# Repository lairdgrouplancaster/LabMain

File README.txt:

How to use this repository:
(Note: All commands are to be entered without quotation marks)

First off, you will need to install Git onto your local machine. Follow this link: "https://git-scm.com/" and download the appropriate version. If unsure whether git is installed on your local machine, open a command prompt and type: "git --version" and see whether it is installed. 

To start with, open up either the command prompt or GitBash and configure your Git username and email, which will be used to identify you as the author for each commit. This is done by entering the following: "git config --global user.name "YOUR_USERNAME"" and "git config --global user.email "YOUR_EMAIL@example.com""

Once this has been done, you can clone the repository to your local device by inputting the following command: "git clone https://github.com/lairdgrouplancaster/LabMain.git" which will then copy all of the files from the repository and place them in a folder of the same name. 

Once cloned, you can navigate to the directory in the command prompt, and then check to see your remote repositories by using: "git remote -v" This will usually show what remote repository it is (usually origin). If this isn't showing, you can manually add these repositories. 

AT THE START OF EACH SESSION: Ensure that you have an up-to-date copy of the repository by using: "git pull origin master"

To check the changes made in the local directory, you can use "git status" to check any modifications that you have made to the file itself, and use "git diff" to view the differences between the local changes to the repository versions that were previously cloned/pulled

You can add changes to the local version of the repository by using the following command: "git add FILE OR FOLDER" or "git add ." to ready either a file, folder or all files and folders for commiting. Then input: "git commit -m "COMMENT ON CHANGE AND INTENTION"" 

To push all of the local commits to the remote repository on GitHub, you can use the following command: "git push origin master", where you can replace origin for the name of a different remote repository and master for a different branch. 

All of this can also be done in the browser as well, and any additional pieces of information (Creating branches, forks etc.) can be found online, usually on the GitHub website itself.

Using a previous version of the repository:

After cloning the repository, look at the recent logs by using the command: "git log --oneline". Select the version of the roll back you want, and then make note of the first 5 characters of the unique number and use: "git checkout (5 characters)". Alternatively, you can use this function based on dates instead, for example if I wanted to revert back 10 days ago, I would input: "git checkout @{10.days.ago}"

Current Files: 

.gitignore: This file tells Git what files and folders to ignore when pulling or pushing updates. Currently only ignores the cache folder for Python.
LICENSE: This is where all licenses for software can be found, and can be added. Currently contains license for GNU
README: Current file, explains how to get started and what files are contained in this repository

Current Folders:

LiamColman: Liam's work uploaded onto Github for storage

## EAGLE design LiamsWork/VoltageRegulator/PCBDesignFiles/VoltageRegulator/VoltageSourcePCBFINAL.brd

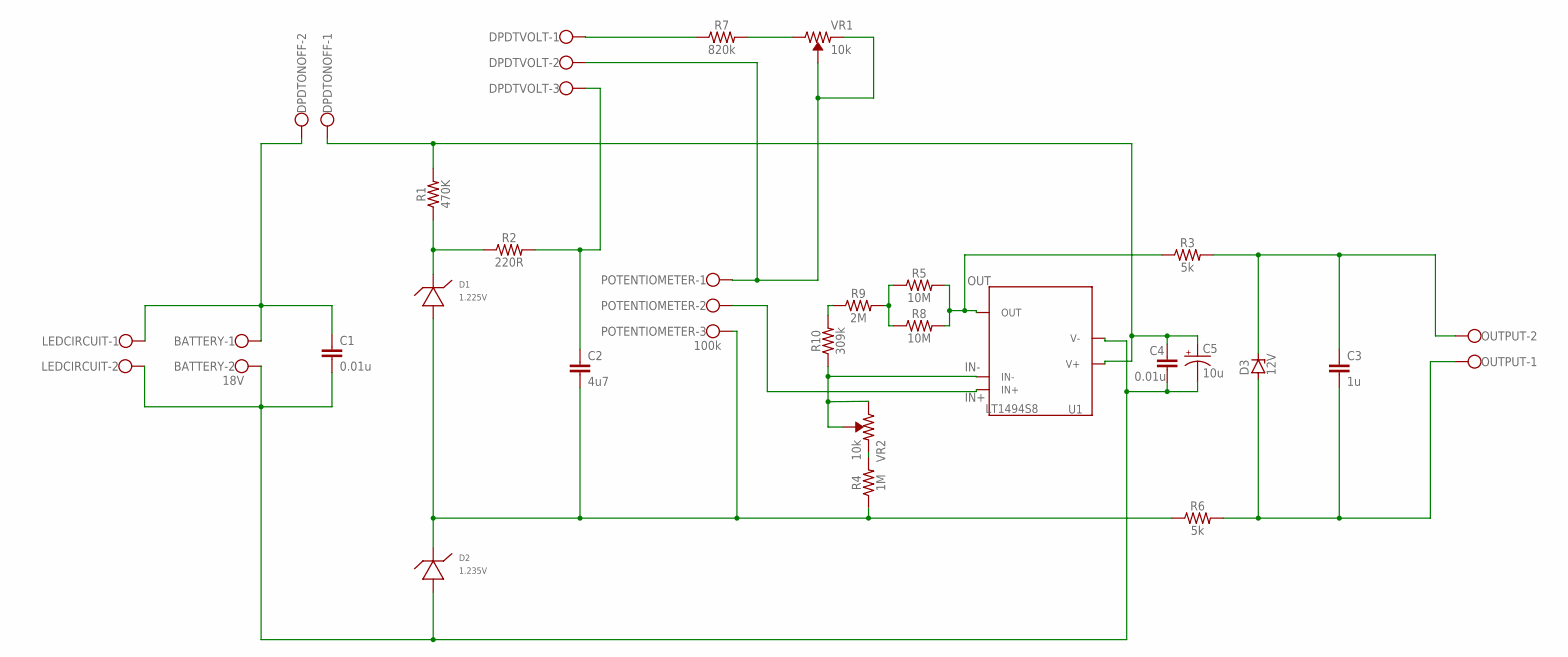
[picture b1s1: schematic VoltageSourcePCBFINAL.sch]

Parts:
BATTERY: 18V; W237-102
C1, C4: 0.01u; 0805
C2: 4u7; 0805
C3: 1u; 0805
C5: 10u; EIA7343
D1: 1.225V; S8PACKAGE
D2: 1.235V; SOIC-8PACKAGE
D3: 12V; SOT23
DPDTONOFF: W237-102
DPDTVOLT: W237-103
LEDCIRCUIT: W237-102
OUTPUT: W237-102
POTENTIOMETER: 100k; W237-103
R1: 470K; 0805
R2: 220R; 0805
R3, R6: 5k; 0805
R4: 1M; 0805
R5, R8: 10M; 0805
R7: 820k; 0805
R9: 2M; 0805
R10: 309k; 0805
U1: LT1494S8; S8PACKAGE
VR1, VR2: 10k; TRIMPOT-SMD-TC33X

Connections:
IN+: POTENTIOMETER.2, U1.3 (IN+)
IN-: R10.1, U1.2 (IN-), VR2.1 (CW), VR2.2 (WIPER)
unnamed: BATTERY.1, C1.1, DPDTONOFF.2, LEDCIRCUIT.1
unnamed: D1.6 (CATHODE), D1.8 (CATHODE), R1.1, R2.1
unnamed: C2.2, D1.4 (ANODE), D2.8 (CATHODE), POTENTIOMETER.3, R4.1, R6.1
unnamed: C2.1, DPDTVOLT.3, R2.2
unnamed: DPDTVOLT.2, POTENTIOMETER.1, VR1.2 (WIPER), VR1.3 (CCW)
unnamed: DPDTVOLT.1, R7.1
unnamed: R5.1, R8.1, R9.2
unnamed: C3.1, D3.3 (C), OUTPUT.2, R3.2
unnamed: C3.2, D3.1 (A), OUTPUT.1, R6.2
unnamed: R4.2, VR2.3 (CCW)
unnamed: R7.2, VR1.1 (CW)
unnamed: R9.1, R10.2
OUT: R3.1, R5.2, R8.2, U1.6 (OUT)
V+: C4.1, C5.A (+), DPDTONOFF.1, R1.2, U1.7 (V+)
V-: BATTERY.2, C1.2, C4.2, C5.C (-), D2.4 (ANODE), LEDCIRCUIT.2, U1.4 (V-)

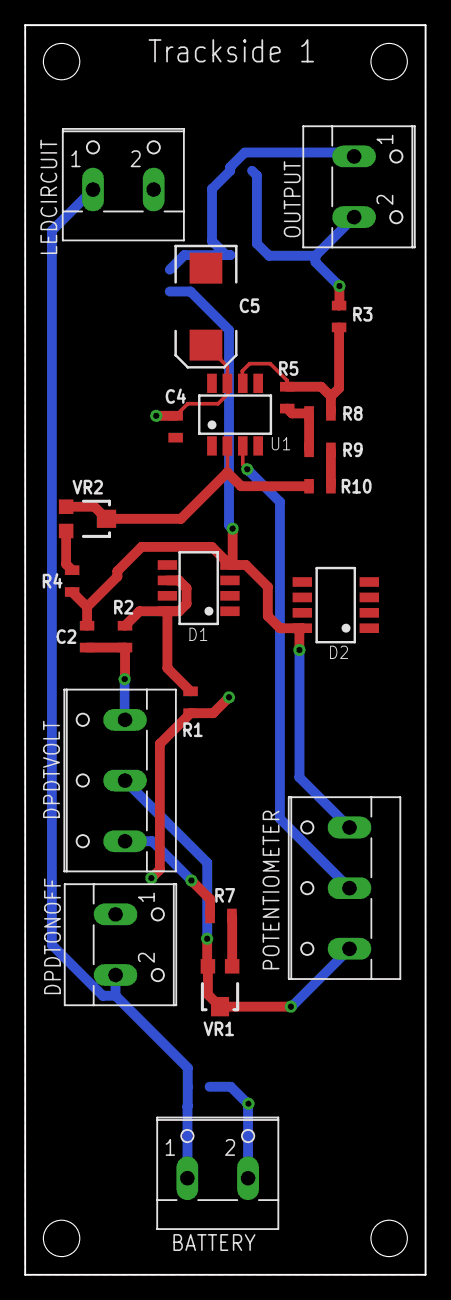
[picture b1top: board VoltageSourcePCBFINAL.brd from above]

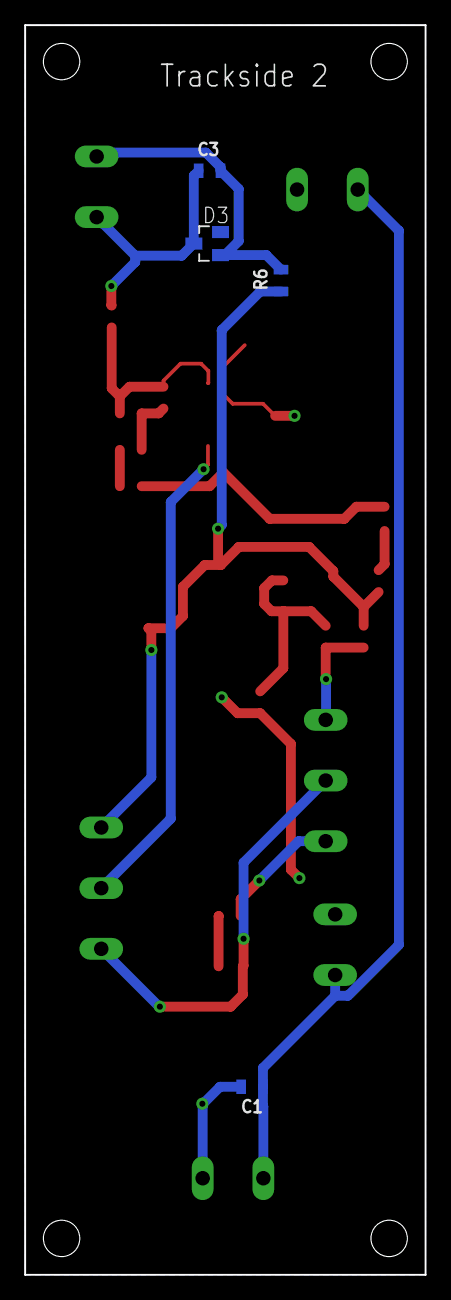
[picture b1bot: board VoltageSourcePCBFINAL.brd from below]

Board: 2 copper layers, 33.0 x 103.0 mm, 27 parts (4 on the bottom side), 17 nets.

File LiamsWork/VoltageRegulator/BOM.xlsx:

| Bill of materials for Voltage Source
 | Part Name | Manufacturer | Manufacturer Part Number | PCB Reference | Qty | Description | SMD or TH | Link | Comment
 | Capacitor | EPCOS | B32529C1103J189 | C1 | 1 | 10nF, DC Film, 100V | TH | Here
 | Capacitor | Panasonic | ECW-FD2E475J | C2 | 1 | 4.7µF, DC Film, 450V | TH | Here
 | Capacitor | Panasonic | ECW-FD2E105J | C3 | 1 | 1µF, DC Film, 450V | TH | There
 | Screw Terminal | CAMDENBOSS | CTB500/2 | LED, Batt, DPDT-On-Off, Out | 4 | 2 pole, Screw | TH | Where
 | Screw Terminal | CAMDENBOSS | CTB500/3 | Potentiometer, DPDT-Voltage-Range | 2 | 3 pole, Screw | TH | Hare
 | Op Amp | LINEAR TECHNOLOGY | LT1494IN8 | U1 | 1 | 1.5µA, 36V supply, Low noise | TH | Lair
 | Resistor | Panasonic | ERA6AEB474V | R1 | 1 | 470k, 0.1%, 0.125W, 0805, Thin film | SMD | Chair
 | Resistor | Panasonic | ERA6AEB221V | R2 | 1 | 220R, 0.1%, 0.125W, 0805, Thin film | SMD | Tear
 | Resistor | Panasonic | ERA6AEB824V | R7 | 1 | 820k, 0.1%, 0.125W, 0805, Thin film | SMD | Bare
 | Resistor | Panasonic | ERA6AEB4993V | R9 | 1 | 499k, 0.1%, 0.125W, 0805, Thin film | SMD | Pear
 | Resistor | TE CONNECTIVITY | CPF-A-0805B1M0E1 | R4 | 1 | 1M, 0.1%, 0.1W, 0805, Thin film | SMD | Bear
 | Resistor | Panasonic | Can't Find Thin Film | R5 | 1 | 6.81M | SMD
 | Resistor | VISHAY | PNM0805E5001BST5 | R3, R6 | 2 | 5k, 0.1%, 0.2W, 0805, Thin Film | SMD | Eclair
 | Trimmer | BOURNS | TC33X-2-104E | VR1 | 1 | 100k trim, 100mW, 1 turn | SMD | Wear
 | Trimmer | BOURNS | TC33X-2-503E | VR2 | 1 | 50k trim, 100mW, 1 turn | SMD | Stair
 | Zener Diode | LINEAR TECHNOLOGY | LT1004-CZ1.2 | D1 | 1 | 1.225V reference, 10µA | TH | Fair
 | Zener Diode | ON Semiconductor | LM385BZ-1.2G | D2 | 1 | 1.235V reference, 10µA | TH | Rare
 | Zener Diode | MULTICOMP | 1N759A | D3 | 1 | 12V reference, 20mA | TH | Mare

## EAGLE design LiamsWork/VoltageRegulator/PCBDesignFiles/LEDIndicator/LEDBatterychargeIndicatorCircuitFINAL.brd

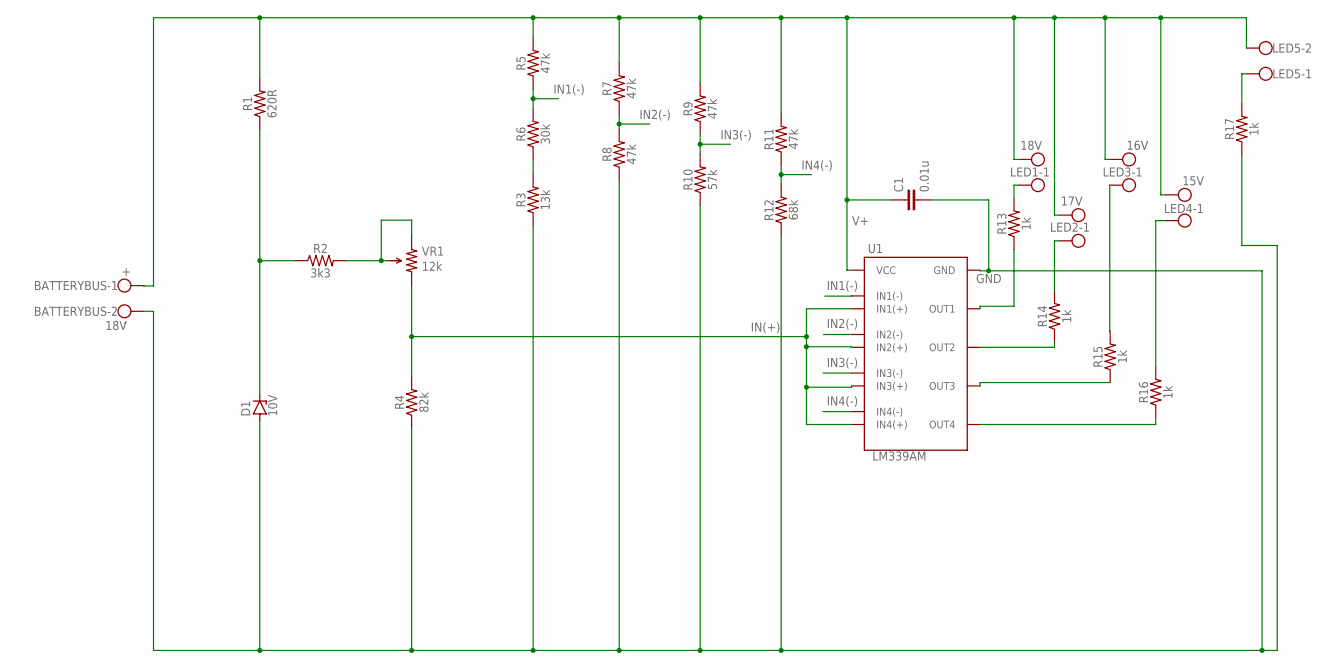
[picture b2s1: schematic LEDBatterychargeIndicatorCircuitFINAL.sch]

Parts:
BATTERYBUS: 18V; W237-102
C1: 0.01u; 0805
D1: 10V; SOT23
LED1: 18V; W237-102
LED2: 17V; W237-102
LED3: 16V; W237-102
LED4: 15V; W237-102
LED5: W237-102
R1: 620R; 0805
R2: 3k3; 0805
R3: 13k; 0805
R4: 82k; 0805
R5, R7, R8, R9, R11: 47k; 0805
R6: 30k; 0805
R10: 57k; 0805
R12: 68k; 0805
R13, R14, R15, R16, R17: 1k; 0805
U1: LM339AM
VR1: 12k; TRIMPOT3266W

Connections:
GND: BATTERYBUS.2, C1.2, D1.1 (A), R3.1, R4.1, R8.1, R10.1, R12.1, R17.1, U1.12 (GND)
IN1(-): R5.1, R6.2, U1.4 (IN1(-))
IN2(-): R7.1, R8.2, U1.6 (IN2(-))
IN3(-): R9.1, R10.2, U1.8 (IN3(-))
IN4(-): R11.1, R12.2, U1.10 (IN4(-))
IN(+): R4.2, U1.5 (IN1(+)), U1.7 (IN2(+)), U1.9 (IN3(+)), U1.11 (IN4(+)), VR1.1
unnamed: LED5.1, R17.2
unnamed: LED1.1, R13.2
unnamed: R13.1, U1.2 (OUT1)
unnamed: D1.3 (C), R1.1, R2.1
unnamed: R14.1, U1.1 (OUT2)
unnamed: R2.2, VR1.2 (WIPER), VR1.3
unnamed: LED2.1, R14.2
unnamed: LED3.1, R15.2
unnamed: R15.1, U1.14 (OUT3)
unnamed: R16.1, U1.13 (OUT4)
unnamed: LED4.1, R16.2
unnamed: R3.2, R6.1
V+: BATTERYBUS.1, C1.1, LED1.2, LED2.2, LED3.2, LED4.2, LED5.2, R1.2, R5.2, R7.2, R9.2, R11.2, U1.3 (VCC)

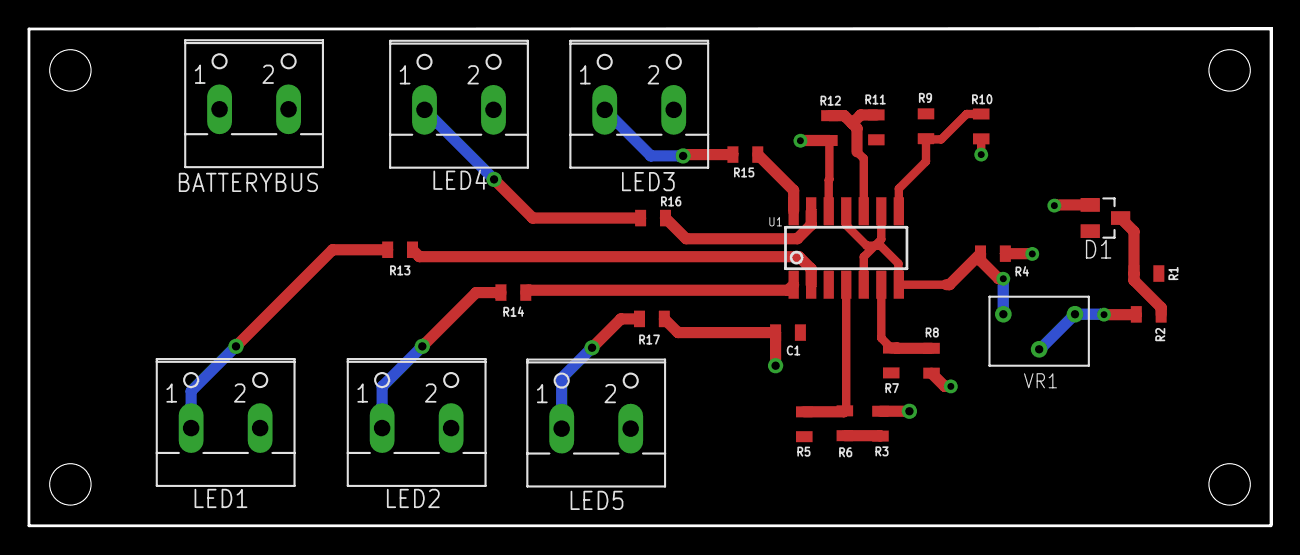
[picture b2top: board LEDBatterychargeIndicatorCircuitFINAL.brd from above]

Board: 2 copper layers, 90.1 x 36.1 mm, 27 parts (0 on the bottom side), 19 nets.

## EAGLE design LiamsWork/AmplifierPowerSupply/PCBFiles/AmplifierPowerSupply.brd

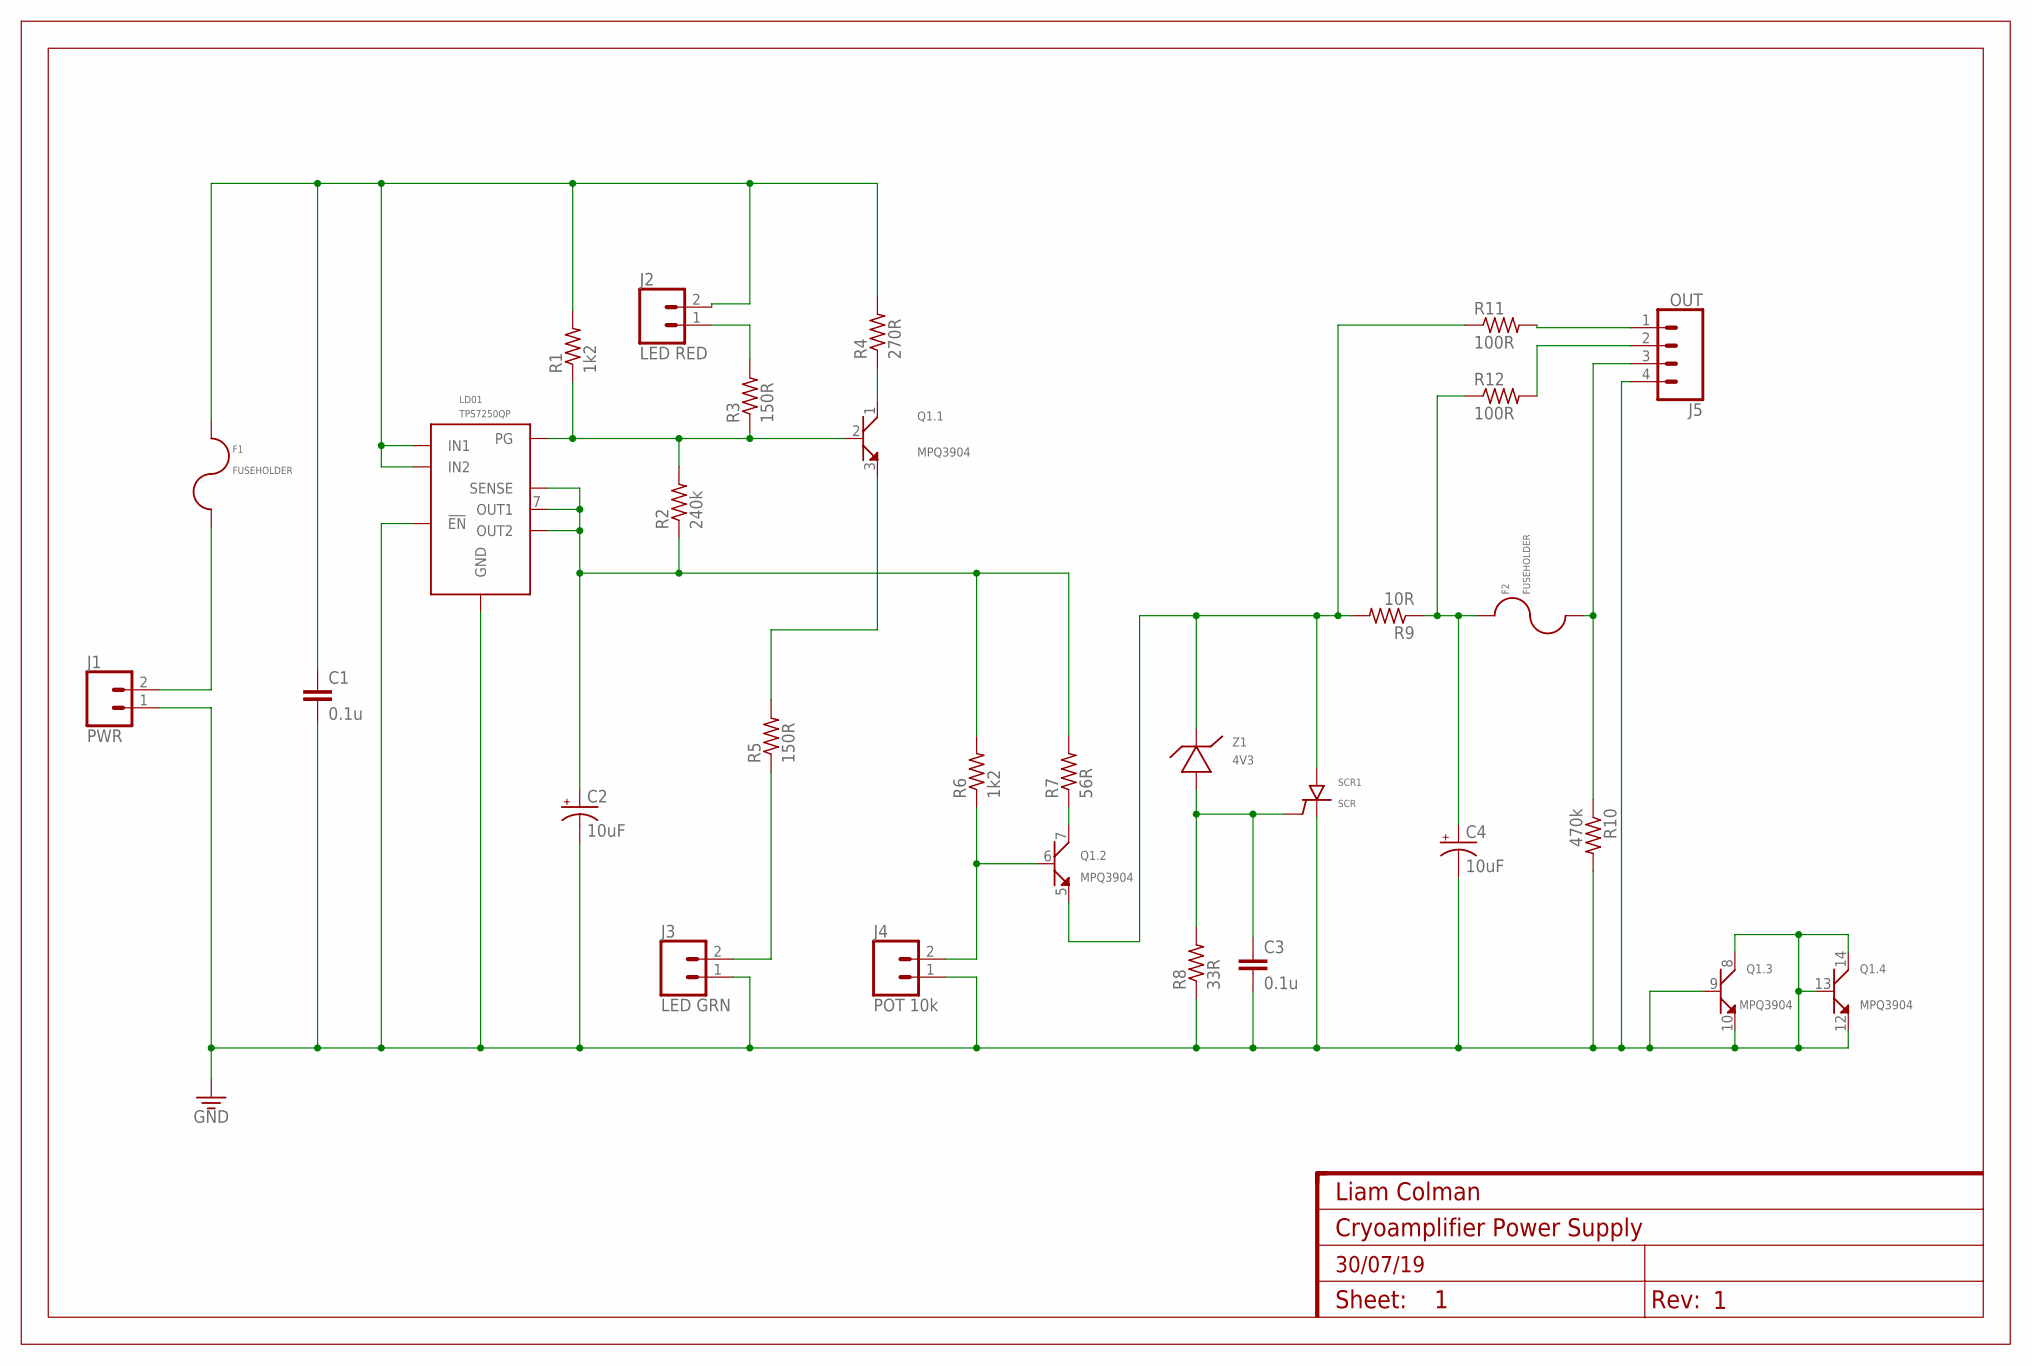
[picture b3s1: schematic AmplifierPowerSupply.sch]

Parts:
C1, C3: 0.1u; C1206K
C2, C4: 10uF; EIA3216
F1, F2: FUSEHOLDER
FRAME1: FRAMELIAM-A4; DUMMY
J1: PWR; 1X02
J2: LED RED; 1X02
J3: LED GRN; 1X02
J4: POT 10k; 1X02
J5: OUT; 1X04
LD01: TPS7250QP
Q1: MPQ3904
R1, R6: 1k2; R0805
R2: 240k; R0805
R3, R5: 150R; R0805
R4: 270R; R0805
R7: 56R; R0805
R8: 33R; R0805
R9: 10R; R0805
R10: 470k; R0805
R11, R12: 100R; R0805
SCR1: SCR; TO-92
Z1: 4V3; DZ2W04300L

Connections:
GND: C1.2, C2.-, C3.2, C4.-, J1.1, J3.1, J4.1, J5.4, LD01.3 (GND), LD01.4 (!EN!), Q1.8 (COLLECTOR), Q1.9 (BASE), Q1.10 (EMITTER), Q1.12 (EMITTER), Q1.13 (BASE), Q1.14 (COLLECTOR), R8.1, R10.2, SCR1.K (CATHODE)
unnamed: F1.P$2, J1.2
unnamed: C1.1, F1.P$1, J2.2, LD01.5 (IN1), LD01.6 (IN2), R1.2, R4.2
unnamed: J2.1, R3.2
unnamed: LD01.2 (PG), Q1.2 (BASE), R1.1, R2.2, R3.1
unnamed: J5.1, R11.2
unnamed: J5.2, R12.2
unnamed: C4.+, F2.P$1, R9.1, R12.1
unnamed: F2.P$2, J5.3, R10.1
unnamed: J4.2, Q1.6 (BASE), R6.1
unnamed: Q1.1 (COLLECTOR), R4.1
unnamed: Q1.3 (EMITTER), R5.2
unnamed: J3.2, R5.1
unnamed: Q1.7 (COLLECTOR), R7.1
unnamed: Q1.5 (EMITTER), R9.2, R11.1, SCR1.A (ANODE), Z1.1 (CATHODE)
unnamed: C2.+, LD01.1 (SENSE), LD01.7 (OUT1), LD01.8 (OUT2), R2.1, R6.2, R7.2
unnamed: C3.1, R8.2, SCR1.G (GATE), Z1.2 (ANODE)

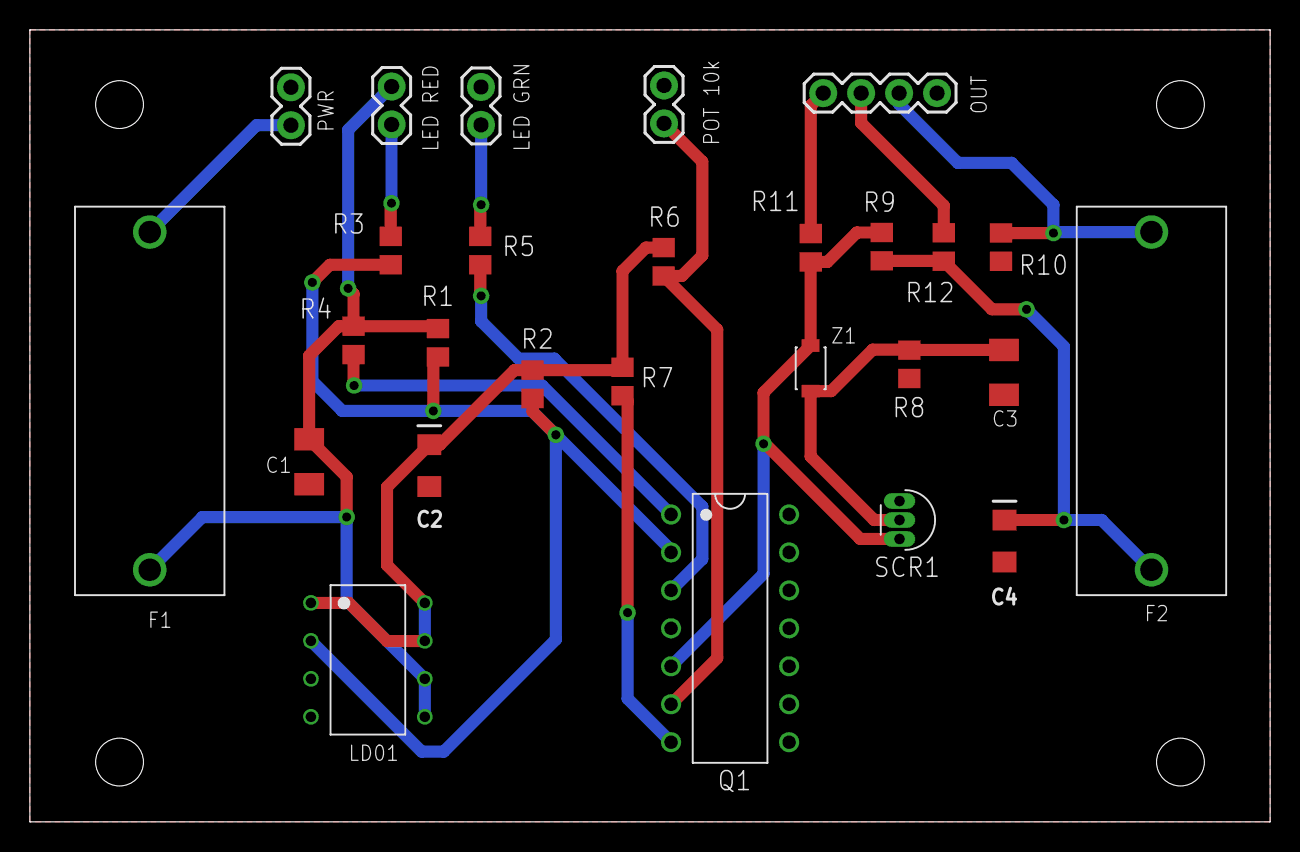
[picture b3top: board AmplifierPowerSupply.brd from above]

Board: 2 copper layers, 83.0 x 53.0 mm, 28 parts (0 on the bottom side), 17 nets.

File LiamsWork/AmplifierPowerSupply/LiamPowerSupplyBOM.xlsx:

| Bill of materials for amplifier power supply
 | Part Name | Manufacturer | Manufacturer Part Number | PCB Reference | Qty | Description | SMD, TH or Other (BGA, QFN etc.) | Comment
 | 1206 Capacitor | PCBTrain Free Stock | 1206-1uF-50V (MC1206B104K500CT) | C1, C3 | 2 | CAPACITOR; 1206; 50V; 10%; X7R; -55+125C | SMD | Farnell
 | 1206 Capacitor | AVX Corporation | TPSA106K010R0900 | C2, C4 | 2 | Tantalum capacitor; 1206; 10V; 10u | SMD |  | Digikey
 | Fuseholder | EATON BUSSMANN SERIES | HTC-100M | F1, F2 | 2 | Fuseholder; 5A; 250V | TH | Farnell
 | 2 pin headers | SULLINS CONNECTOR SOLUTIONS | GEC01DAAN | J1, J2, J3, J4 | 4 | Male header; 2 pin; 2 row; 2.54mm pitch | TH |  | Digikey
 | 4 pin header | SULLINS CONNECTOR SOLUTIONS | PEC04SAAN | J5 | 1 | Male header; 4 pin; 1 row; 2.54mm pitch | TH |  | Digikey
 | Low-Dropout voltage regulator | TEXAS INSTRUMENTS | TPS7250 | LD01 | 1 | 5V output; low quiescent current; power good status; PDIP package | TH | Mouser | Texas Instuments
 | DIP Socket | Winslow | W30508TRC | LD01 | 1 | 8 pin; 7.62mm row spacing; 2.54mm pitch | TH |  | RS Components
 | Quad transistors | CENTRAL SEMICONDUCTOR | MPQ3904 | Q1 | 1 | Quad bipolar transistors; NPN; TO-116 package | TH | Mouser
 | DIP Socket | ARIES | 14-3518-10 | Q1 | 1 | 14 pin; 7.62mm row spacing; 2.54mm pitch | TH | Farnell
 | 0805 Resistor | PCBTrain Free Stock | 0805-1K2 | R1, R6 | 2 | RESISTOR; 0805; 0.125W; 100ppm; 1%; 150V; -55+125C; 1.2k | SMD
 | 0805 Resistor | PCBTrain Free Stock | 0805-240K | R2 | 1 | RESISTOR; 0805; 0.125W; 100ppm; 1%; 150V; -55+125C; 240k | SMD
 | 0805 Resistor | PCBTrain Free Stock | 0805-150R | R3, R5 | 2 | RESISTOR; 0805; 0.125W; 100ppm; 1%; 150V; -55+125C; 150R | SMD
 | 0805 Resistor | PCBTrain Free Stock | 0805-270R | R4 | 1 | RESISTOR; 0805; 0.125W; 100ppm; 1%; 150V; -55+125C; 270R | SMD
 | 0805 Resistor | PCBTrain Free Stock | 0805-56R | R7 | 1 | RESISTOR; 0805; 0.125W; 100ppm; 1%; 150V; -55+125C; 56R | SMD
 | 0805 Resistor | PCBTrain Free Stock | 0805-33R | R8 | 1 | RESISTOR; 0805; 0.125W; 100ppm; 1%; 150V; -55+125C: 33R | SMD
 | 0805 Resistor | PCBTrain Free Stock | 0805-10R | R9 | 1 | RESISTOR; 0805; 0.125W; 100ppm; 1%; 150V; -55+125C; 10R | SMD
 | 0805 Resistor | PCBTrain Free Stock | 0805-470K | R10 | 1 | RESISTOR; 0805; 0.125W; 100ppm; 1%; 150V; -55+125C; 470k | SMD
 | 0805 Resistor | PCBTrain Free Stock | 0805-100R | R11, R12 | 2 | RESISTOR; 0805; 0.125W; 100ppm; 1%; 150V; -55+125C; 100R | SMD
 | Thryristor | STMicroelectronics | X0205MA 1BA2 | SCR1 | 1 | 1.25A sensitive gate SCR | TH | Mouser
 | Zener diode | Panasonic | DZ2W04300L | Z1 | 1 | 4.3V zener diode; Mini2 package | SMD | Mouser | Digikey

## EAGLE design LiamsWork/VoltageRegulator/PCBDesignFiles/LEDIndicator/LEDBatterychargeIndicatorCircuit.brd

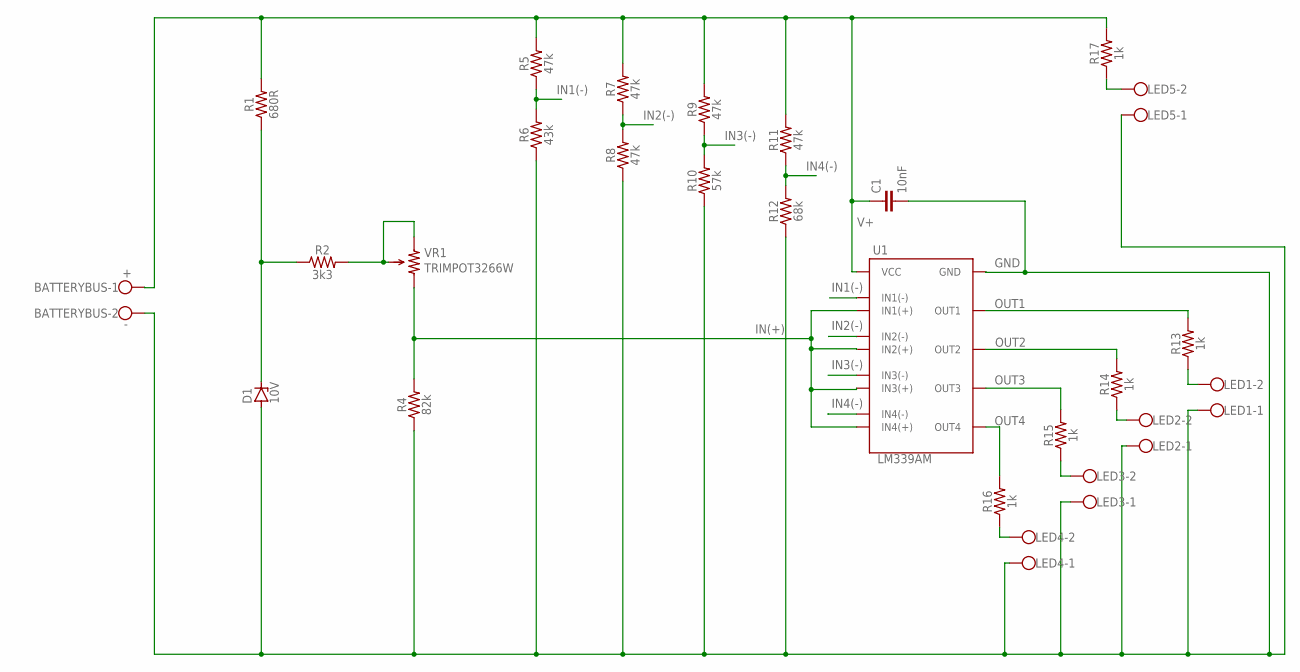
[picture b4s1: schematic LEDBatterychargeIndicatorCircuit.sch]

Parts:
BATTERYBUS: W237-102
C1: 10nF; C7.5B5
D1: 10V; F126Z12
LED1, LED2, LED3, LED4, LED5: W237-102
R1: 680R; 0805
R2: 3k3; 0805
R4: 82k; 0805
R5, R7, R8, R9, R11: 47k; 0805
R6: 43k; 0805
R10: 57k; 0805
R12: 68k; 0805
R13, R14, R15, R16, R17: 1k; 0805
U1: LM339AM
VR1: TRIMPOT3266W

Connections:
GND: BATTERYBUS.2, C1.2, D1.A, LED1.1, LED2.1, LED3.1, LED4.1, LED5.1, R4.1, R6.1, R8.1, R10.1, R12.1, U1.12 (GND)
IN1(-): R5.1, R6.2, U1.4 (IN1(-))
IN2(-): R7.1, R8.2, U1.6 (IN2(-))
IN3(-): R9.1, R10.2, U1.8 (IN3(-))
IN4(-): R11.1, R12.2, U1.10 (IN4(-))
IN(+): R4.2, U1.5 (IN1(+)), U1.7 (IN2(+)), U1.9 (IN3(+)), U1.11 (IN4(+)), VR1.1
unnamed: D1.C, R1.1, R2.1
unnamed: R2.2, VR1.2 (WIPER), VR1.3
unnamed: LED1.2, R13.1
unnamed: LED2.2, R14.1
unnamed: LED3.2, R15.1
unnamed: LED4.2, R16.1
unnamed: LED5.2, R17.1
OUT1: R13.2, U1.2 (OUT1)
OUT2: R14.2, U1.1 (OUT2)
OUT3: R15.2, U1.14 (OUT3)
OUT4: R16.2, U1.13 (OUT4)
V+: BATTERYBUS.1, C1.1, R1.2, R5.2, R7.2, R9.2, R11.2, R17.2, U1.3 (VCC)

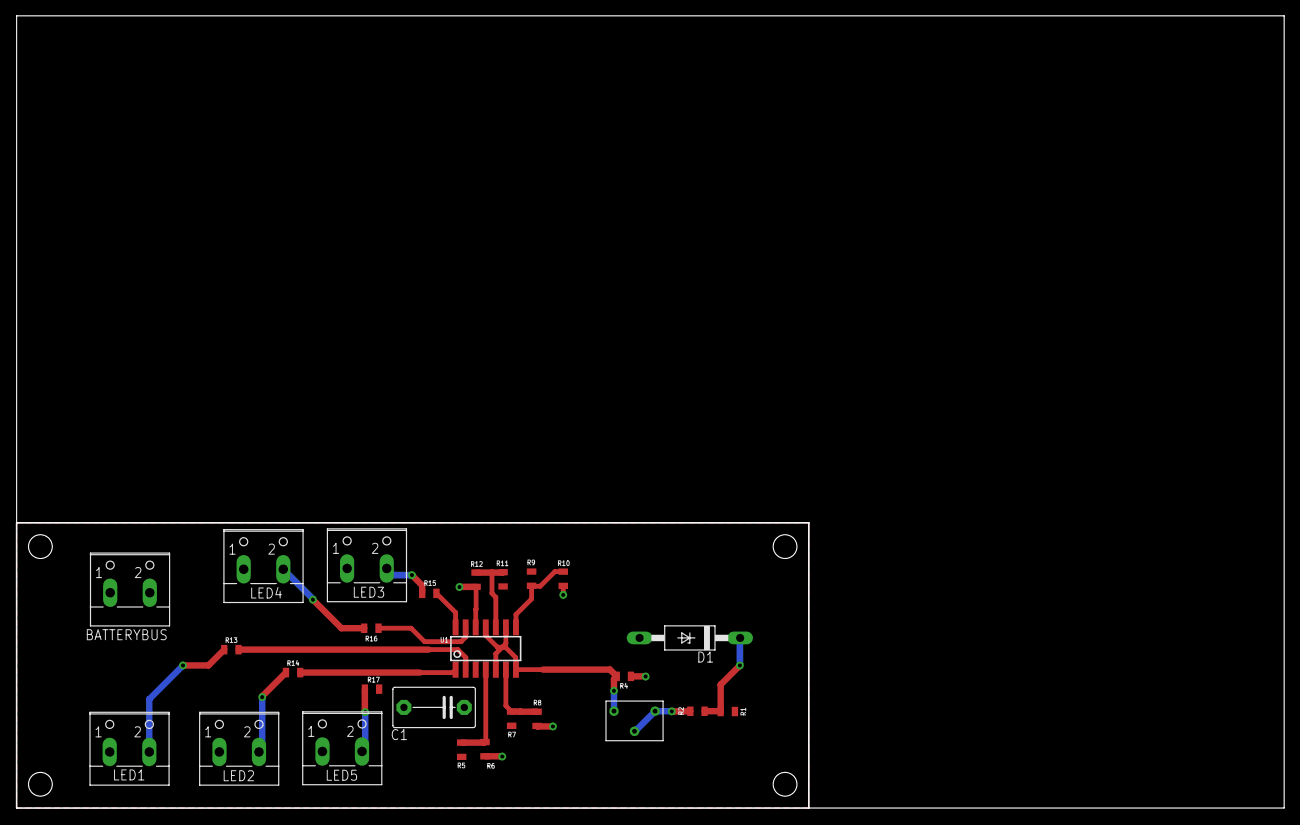
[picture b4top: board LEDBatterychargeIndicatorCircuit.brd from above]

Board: 2 copper layers, 160.0 x 100.0 mm, 26 parts (0 on the bottom side), 18 nets.

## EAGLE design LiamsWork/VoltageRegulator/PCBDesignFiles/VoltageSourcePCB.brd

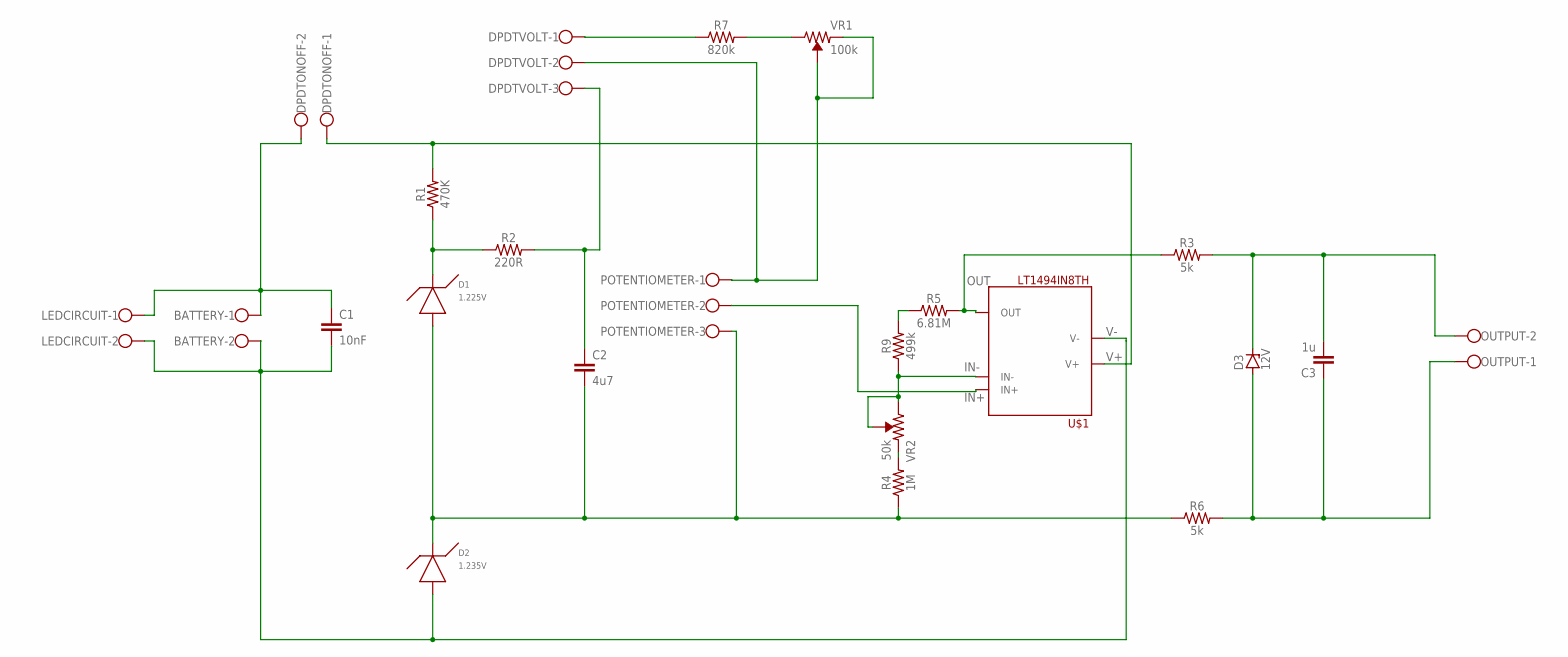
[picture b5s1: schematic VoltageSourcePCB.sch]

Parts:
BATTERY: W237-102
C1: 10nF; C5B2.5
C2: 4u7; C22.5B11
C3: 1u; C150-072X183
D1: 1.225V; LT1004CZ
D2: 1.235V; LT1004CZ
D3: 12V; C1702-15
DPDTONOFF: W237-102
DPDTVOLT: W237-103
LEDCIRCUIT: W237-102
OUTPUT: W237-102
POTENTIOMETER: W237-103
R1: 470K; 0805
R2: 220R; 0805
R3, R6: 5k; 0805
R4: 1M; 0805
R5: 6.81M; 0805
R7: 820k; 0805
R9: 499k; 0805
U$1: LT1494IN8TH; LT1494TH
VR1: 100k; TRIMPOT-SMD-TC33X
VR2: 50k; TRIMPOT-SMD-TC33X

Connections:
IN+: POTENTIOMETER.2, U$1.3 (IN+)
IN-: R9.1, U$1.2 (IN-), VR2.1 (CW), VR2.2 (WIPER)
unnamed: D1.CATHODE, R1.1, R2.1
unnamed: C2.2, D1.ANODE, D2.CATHODE, POTENTIOMETER.3, R4.1, R6.1
unnamed: C2.1, DPDTVOLT.3, R2.2
unnamed: DPDTVOLT.2, POTENTIOMETER.1, VR1.2 (WIPER), VR1.3 (CCW)
unnamed: DPDTVOLT.1, R7.1
unnamed: BATTERY.1, C1.1, DPDTONOFF.2, LEDCIRCUIT.1
unnamed: C3.2, D3.C, OUTPUT.2, R3.2
unnamed: C3.1, D3.A, OUTPUT.1, R6.2
unnamed: R4.2, VR2.3 (CCW)
unnamed: R7.2, VR1.1 (CW)
unnamed: R5.1, R9.2
OUT: R3.1, R5.2, U$1.6 (OUT)
V+: DPDTONOFF.1, R1.2, U$1.7 (V+)
V-: BATTERY.2, C1.2, D2.ANODE, LEDCIRCUIT.2, U$1.4 (V-)

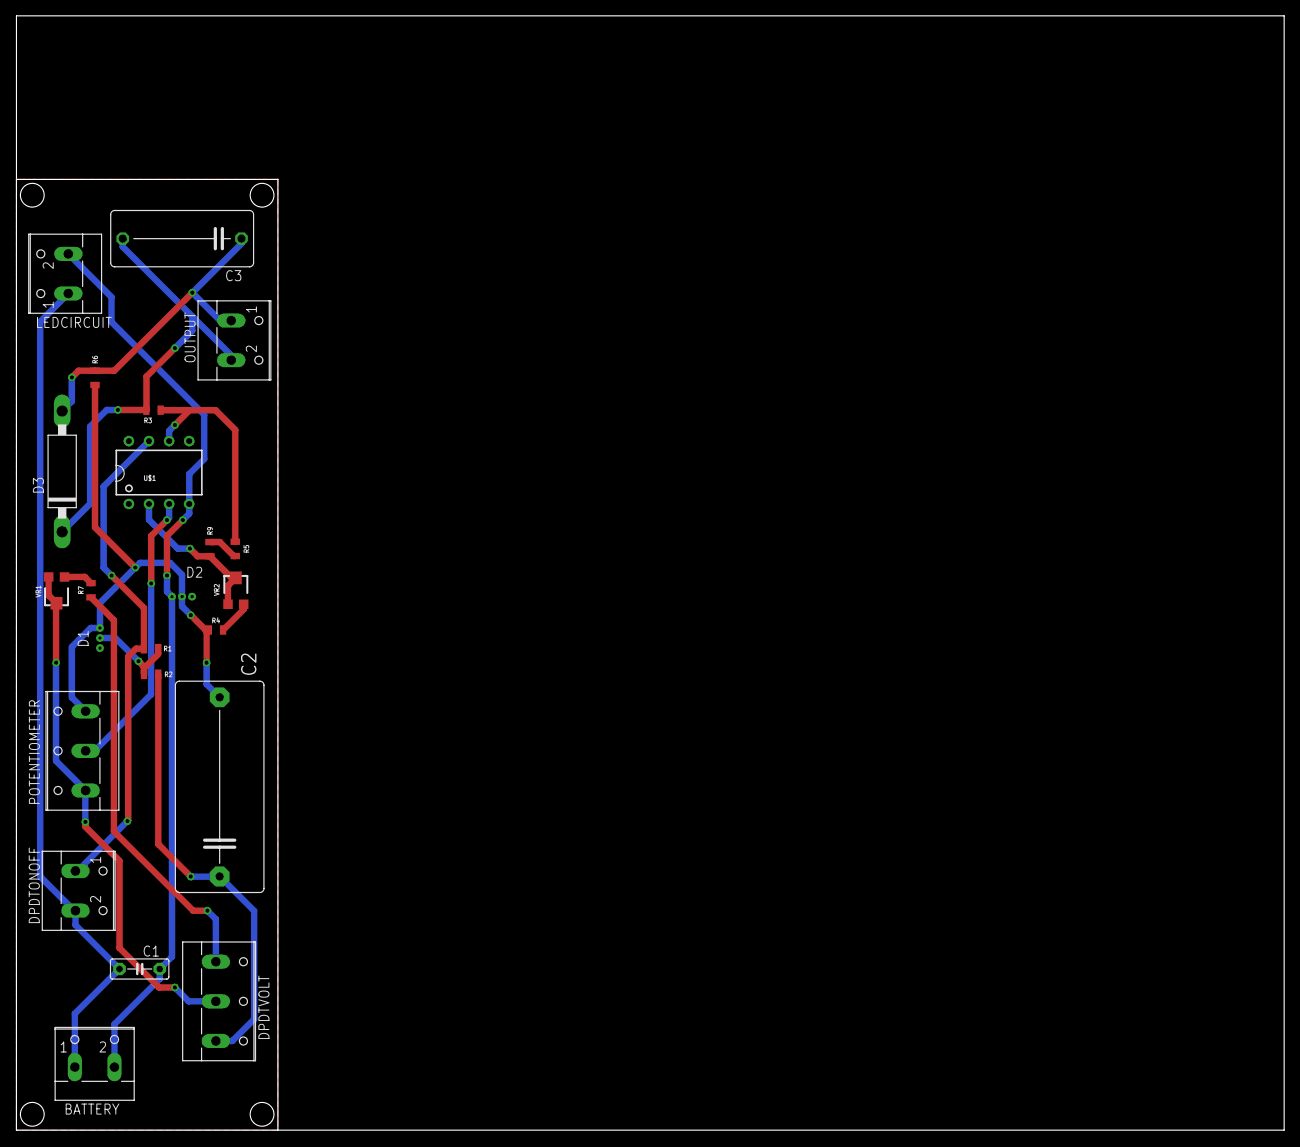
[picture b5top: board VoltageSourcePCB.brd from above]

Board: 2 copper layers, 160.0 x 140.6 mm, 23 parts (0 on the bottom side), 16 nets.

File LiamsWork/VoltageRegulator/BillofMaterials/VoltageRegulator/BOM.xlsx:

| Bill of materials for Voltage Source
 | Part Name | Manufacturer | Manufacturer Part Number | PCB Reference | Qty | Description | SMD or TH | Link | Comment
 | Capacitor | EPCOS | B32529C1103J189 | C1 | 1 | 10nF, DC Film, 100V | TH | Here
 | Capacitor | Panasonic | ECW-FD2E475J | C2 | 1 | 4.7µF, DC Film, 450V | TH | Here
 | Capacitor | Panasonic | ECW-FD2E105J | C3 | 1 | 1µF, DC Film, 450V | TH | There
 | Screw Terminal | CAMDENBOSS | CTB500/2 | LED, Batt, DPDT-On-Off, Out | 4 | 2 pole, Screw | TH | Where
 | Screw Terminal | CAMDENBOSS | CTB500/3 | Potentiometer, DPDT-Voltage-Range | 2 | 3 pole, Screw | TH | Hare
 | Op Amp | LINEAR TECHNOLOGY | LT1494IN8 | U1 | 1 | 1.5µA, 36V supply, Low noise | TH | Lair
 | Resistor | Panasonic | ERA6AEB474V | R1 | 1 | 470k, 0.1%, 0.125W, 0805, Thin film | SMD | Chair
 | Resistor | Panasonic | ERA6AEB221V | R2 | 1 | 220R, 0.1%, 0.125W, 0805, Thin film | SMD | Tear
 | Resistor | Panasonic | ERA6AEB824V | R7 | 1 | 820k, 0.1%, 0.125W, 0805, Thin film | SMD | Bare
 | Resistor | Panasonic | ERA6AEB4993V | R9 | 1 | 499k, 0.1%, 0.125W, 0805, Thin film | SMD | Pear
 | Resistor | TE CONNECTIVITY | CPF-A-0805B1M0E1 | R4 | 1 | 1M, 0.1%, 0.1W, 0805, Thin film | SMD | Bear
 | Resistor | Panasonic | Can't Find Thin Film | R5 | 1 | 6.81M | SMD
 | Resistor | VISHAY | PNM0805E5001BST5 | R3, R6 | 2 | 5k, 0.1%, 0.2W, 0805, Thin Film | SMD | Eclair
 | Trimmer | BOURNS | TC33X-2-104E | VR1 | 1 | 100k trim, 100mW, 1 turn | SMD | Wear
 | Trimmer | BOURNS | TC33X-2-503E | VR2 | 1 | 50k trim, 100mW, 1 turn | SMD | Stair
 | Zener Diode | LINEAR TECHNOLOGY | LT1004-CZ1.2 | D1 | 1 | 1.225V reference, 10µA | TH | Fair
 | Zener Diode | ON Semiconductor | LM385BZ-1.2G | D2 | 1 | 1.235V reference, 10µA | TH | Rare
 | Zener Diode | MULTICOMP | 1N759A | D3 | 1 | 12V reference, 20mA | TH | Mare

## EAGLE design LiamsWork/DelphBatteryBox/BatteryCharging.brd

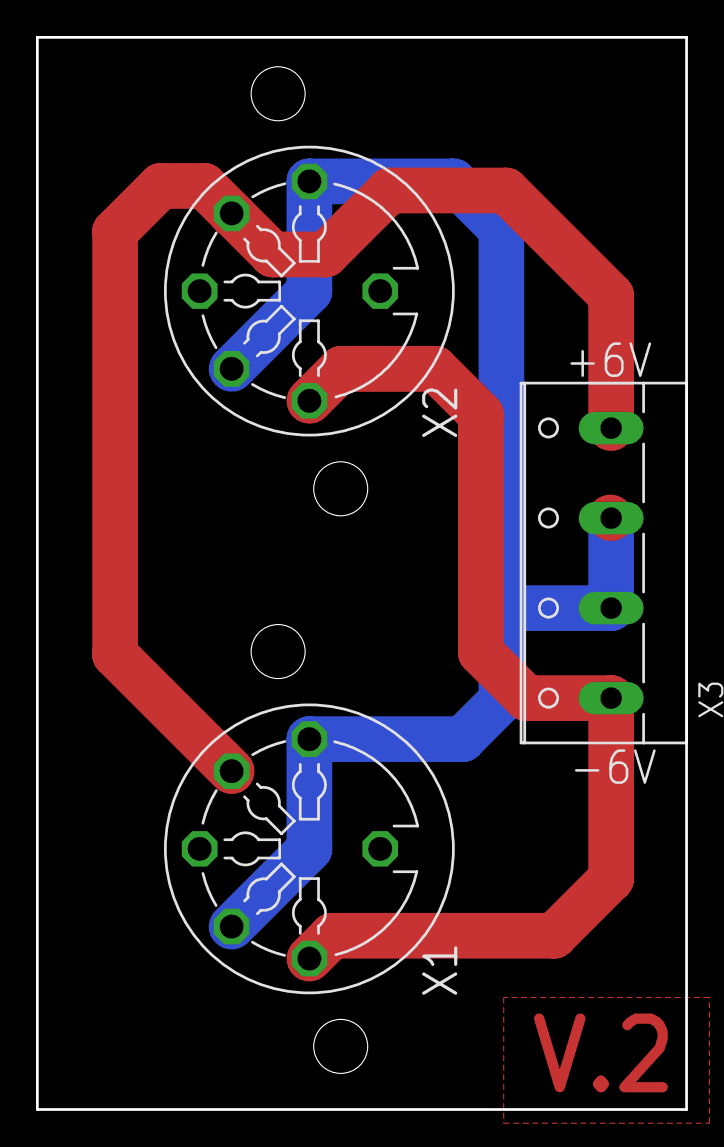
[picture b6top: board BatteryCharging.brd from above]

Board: 2 copper layers, 36.1 x 59.6 mm, 3 parts (0 on the bottom side), 4 nets.

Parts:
X1, X2: MAB5SV
X3: W237-4

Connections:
0V: X1.3, X1.4, X2.3, X2.4, X3.2, X3.3
+6V: X1.5, X2.5, X3.4
-6V: X1.1, X2.1, X3.1
GND: X1.2, X1.PE, X2.2, X2.PE

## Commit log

2019-06-24 Readme & ignore file added
2019-06-24 Modified Readme
2019-06-24 Add Liam folder
2019-06-25 Typo correction in README
2019-06-25 Added research on components to use
2019-06-25 Adjustment of component list
2019-06-25 Adjustment of component list 2
2019-06-25 Added additional screw terminal
2019-06-26 Small update to component list
2019-06-27 Updated Battery PCB files
2019-06-28 Updated PCB design & Gerber files
2019-07-10 Changed name of repository and added voltage source files
2019-07-10 Altered file path for Voltage Source files and Battery box files
2019-08-16 Files updated to contain recent developments, added Amplifier power supply file
2019-10-04 Added updated files for all of the things I've done at the end of the internship
2025-03-17 connect 0V between both batteries
2025-03-17 version number on board
2025-03-17 adjust connector mounting holes

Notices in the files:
parts and their libraries:
SparkFun-Capacitors: Licensing: Creative Commons ShareAlike 4.0 International - https://creativecommons.org/licenses/by-sa/4.0
